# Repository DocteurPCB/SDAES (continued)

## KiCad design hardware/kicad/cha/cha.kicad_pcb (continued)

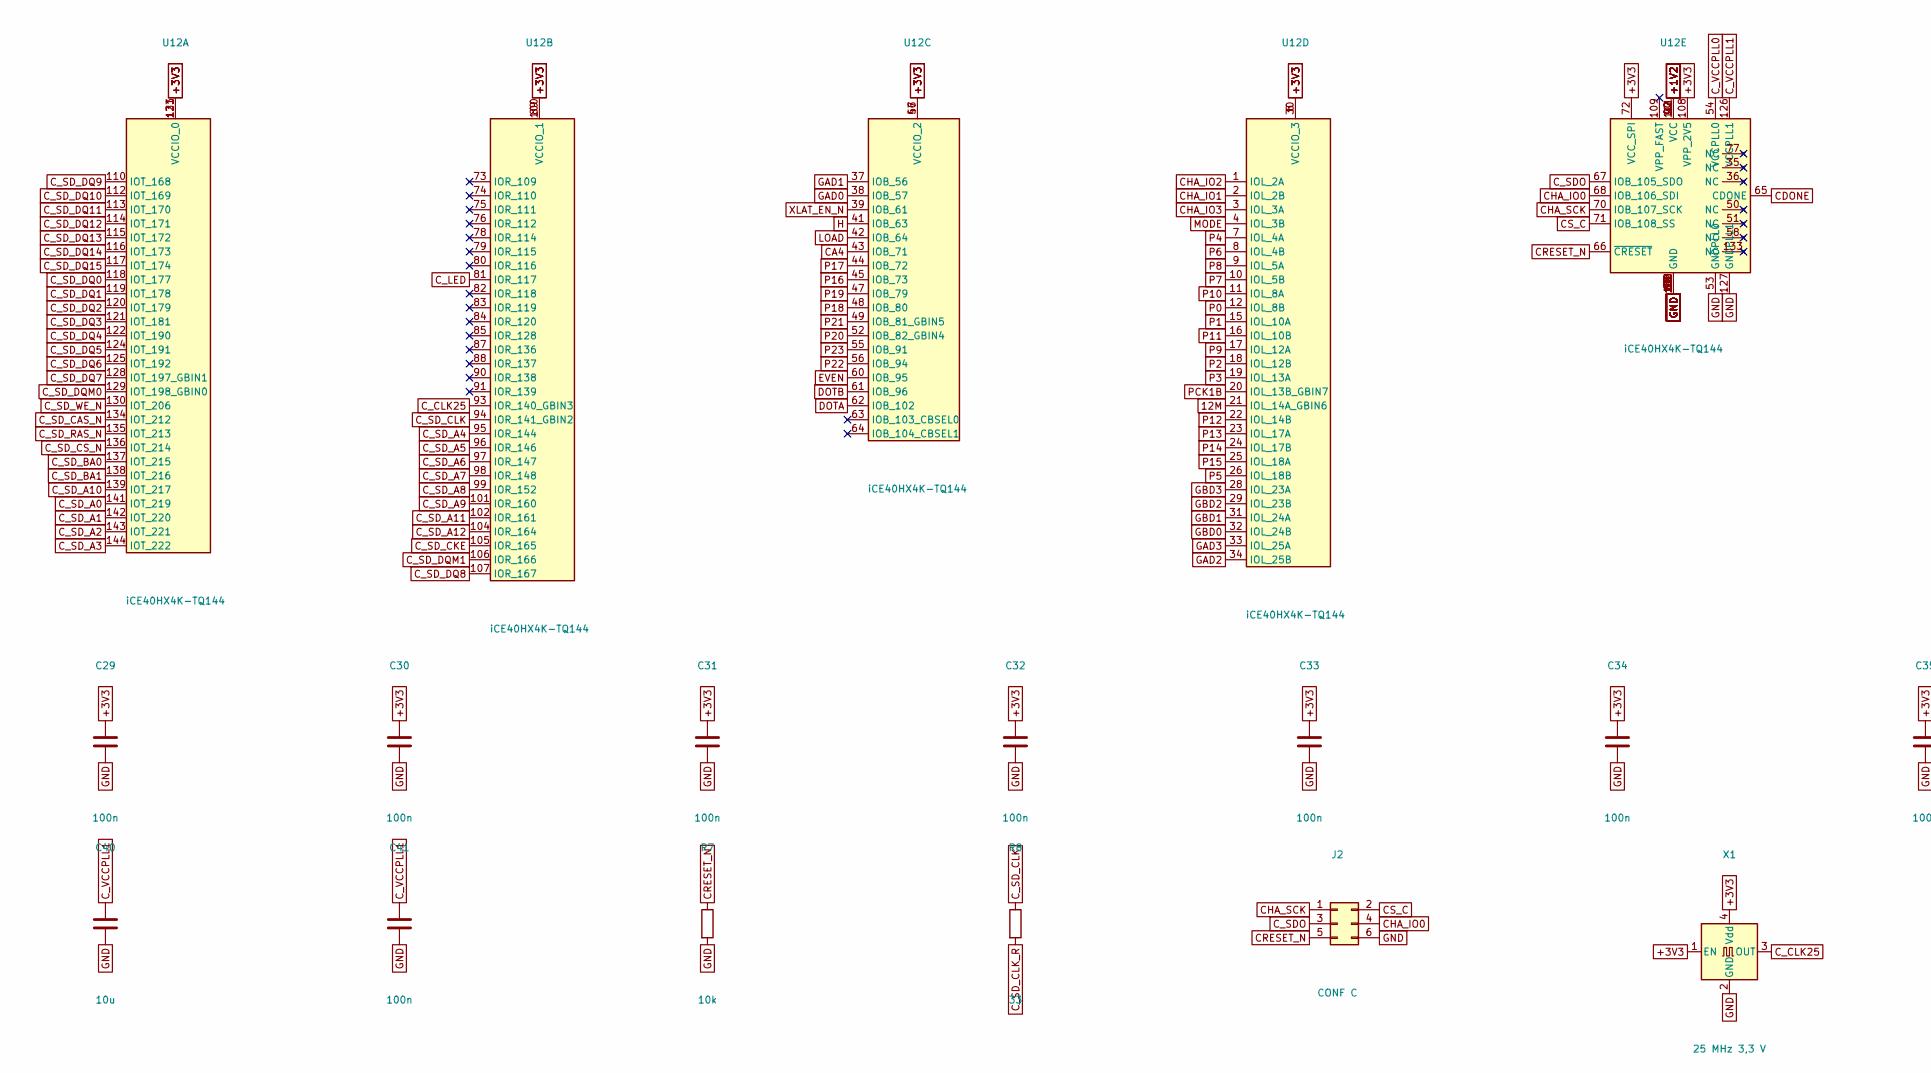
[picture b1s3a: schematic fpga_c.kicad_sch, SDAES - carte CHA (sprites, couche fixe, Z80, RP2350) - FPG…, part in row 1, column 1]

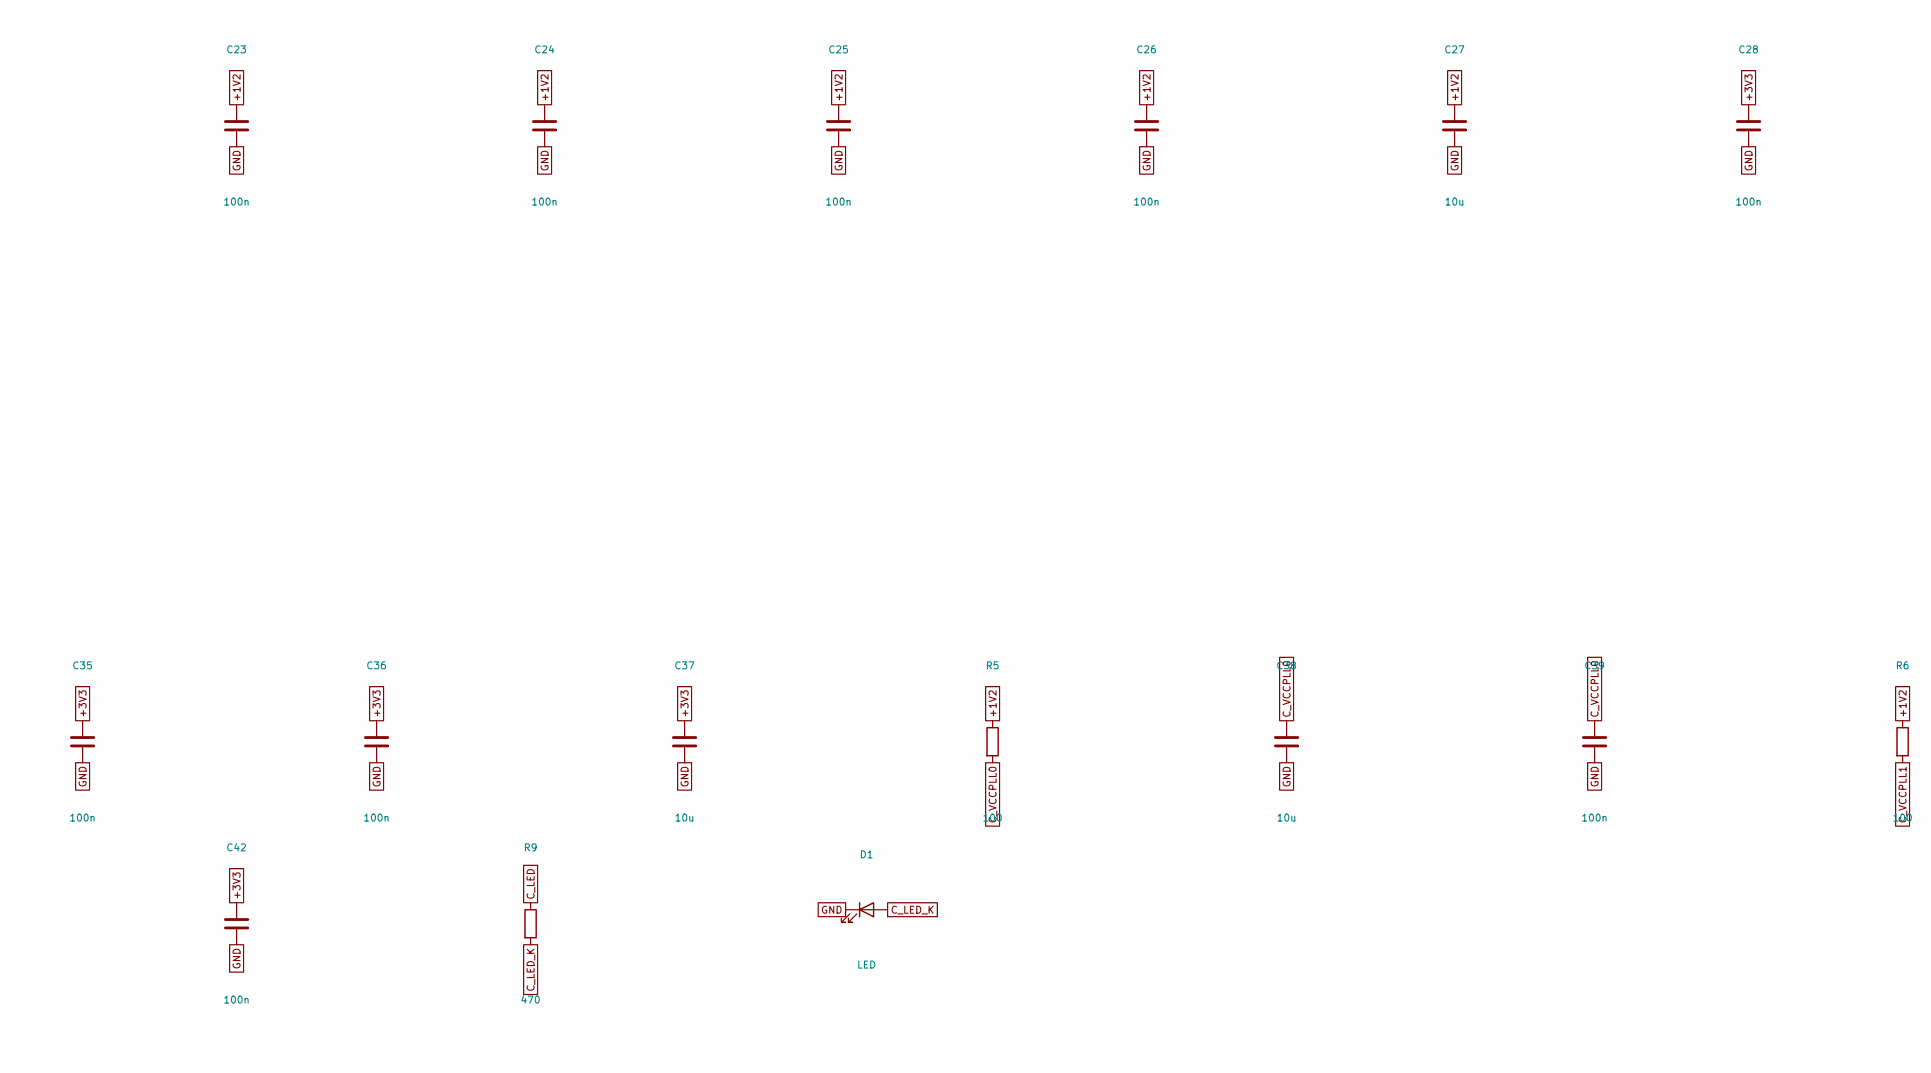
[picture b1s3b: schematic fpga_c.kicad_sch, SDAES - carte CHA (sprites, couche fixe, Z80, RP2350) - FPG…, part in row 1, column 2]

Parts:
C23, C24, C25, C26, C28, C29, C30, C31, C32, C33, C34, C35, C36, C39, C41, C42: 100n; C_0603_1608Metric
C27, C37, C38, C40: 10u; C_0805_2012Metric
D1: LED; LED_0603_1608Metric
J2: CONF C; PinHeader_2x03_P2.54mm_Vertical
R5, R6: 100; R_0603_1608Metric
R7: 10k; R_0603_1608Metric
R8: 33; R_0603_1608Metric
R9: 470; R_0603_1608Metric
U12: iCE40HX4K-TQ144; TQFP-144_20x20mm_P0.5mm
X1: 25 MHz 3,3 V; Oscillator_SMD_Abracon_ASE-4Pin_3.2x2.5mm_HandSoldering

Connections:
12M: U12.21 (IOL_14A_GBIN6); also elsewhere on the board
+1V2: C23.1, C24.1, C25.1, C26.1, C27.1, R5.1, R6.1, U12.27 (VCC), U12.40 (VCC), U12.92 (VCC), U12.111 (VCC); also elsewhere on the board
+3V3: C28.1, C29.1, C30.1, C31.1, C32.1, C33.1, C34.1, C35.1, C36.1, C37.1, C42.1, U12.6 (VCCIO_3), U12.30 (VCCIO_3), U12.46 (VCCIO_2), U12.57 (VCCIO_2), U12.72 (VCC_SPI), U12.89 (VCCIO_1), U12.100 (VCCIO_1), U12.108 (VPP_2V5), U12.123 (VCCIO_0), U12.131 (VCCIO_0), X1.1 (EN), X1.4 (Vdd); also elsewhere on the board
CA4: U12.43 (IOB_71); also elsewhere on the board
CDONE: U12.65 (CDONE); also elsewhere on the board
CHA_IO0: J2.4, U12.68 (IOB_106_SDI); also elsewhere on the board
CHA_IO1: U12.2 (IOL_2B); also elsewhere on the board
CHA_IO2: U12.1 (IOL_2A); also elsewhere on the board
CHA_IO3: U12.3 (IOL_3A); also elsewhere on the board
CHA_SCK: J2.1, U12.70 (IOB_107_SCK); also elsewhere on the board
CRESET_N: J2.5, R7.1, U12.66 (~CRESET); also elsewhere on the board
CS_C: J2.2, U12.71 (IOB_108_SS); also elsewhere on the board
C_CLK25: U12.93 (IOR_140_GBIN3), X1.3 (OUT)
C_LED: R9.1, U12.81 (IOR_117)
C_LED_K: D1.2 (A), R9.2
C_SDO: J2.3, U12.67 (IOB_105_SDO)
C_SD_A0: U12.141 (IOT_219); also elsewhere on the board
C_SD_A1: U12.142 (IOT_220); also elsewhere on the board
C_SD_A2: U12.143 (IOT_221); also elsewhere on the board
C_SD_A3: U12.144 (IOT_222); also elsewhere on the board
C_SD_A4: U12.95 (IOR_144); also elsewhere on the board
C_SD_A5: U12.96 (IOR_146); also elsewhere on the board
C_SD_A6: U12.97 (IOR_147); also elsewhere on the board
C_SD_A7: U12.98 (IOR_148); also elsewhere on the board
C_SD_A8: U12.99 (IOR_152); also elsewhere on the board
C_SD_A9: U12.101 (IOR_160); also elsewhere on the board
C_SD_A10: U12.139 (IOT_217); also elsewhere on the board
C_SD_A11: U12.102 (IOR_161); also elsewhere on the board
C_SD_A12: U12.104 (IOR_164); also elsewhere on the board
C_SD_BA0: U12.137 (IOT_215); also elsewhere on the board
C_SD_BA1: U12.138 (IOT_216); also elsewhere on the board
C_SD_CAS_N: U12.134 (IOT_212); also elsewhere on the board
C_SD_CKE: U12.105 (IOR_165); also elsewhere on the board
C_SD_CLK: R8.1, U12.94 (IOR_141_GBIN2)
C_SD_CLK_R: R8.2; also elsewhere on the board
C_SD_CS_N: U12.136 (IOT_214); also elsewhere on the board
C_SD_DQ0: U12.118 (IOT_177); also elsewhere on the board
C_SD_DQ1: U12.119 (IOT_178); also elsewhere on the board
C_SD_DQ2: U12.120 (IOT_179); also elsewhere on the board
C_SD_DQ3: U12.121 (IOT_181); also elsewhere on the board
C_SD_DQ4: U12.122 (IOT_190); also elsewhere on the board
C_SD_DQ5: U12.124 (IOT_191); also elsewhere on the board
C_SD_DQ6: U12.125 (IOT_192); also elsewhere on the board
C_SD_DQ7: U12.128 (IOT_197_GBIN1); also elsewhere on the board
C_SD_DQ8: U12.107 (IOR_167); also elsewhere on the board
C_SD_DQ9: U12.110 (IOT_168); also elsewhere on the board
C_SD_DQ10: U12.112 (IOT_169); also elsewhere on the board
C_SD_DQ11: U12.113 (IOT_170); also elsewhere on the board
C_SD_DQ12: U12.114 (IOT_171); also elsewhere on the board
C_SD_DQ13: U12.115 (IOT_172); also elsewhere on the board
C_SD_DQ14: U12.116 (IOT_173); also elsewhere on the board
C_SD_DQ15: U12.117 (IOT_174); also elsewhere on the board
C_SD_DQM0: U12.129 (IOT_198_GBIN0); also elsewhere on the board
C_SD_DQM1: U12.106 (IOR_166); also elsewhere on the board
C_SD_RAS_N: U12.135 (IOT_213); also elsewhere on the board
C_SD_WE_N: U12.130 (IOT_206); also elsewhere on the board
C_VCCPLL0: C38.1, C39.1, R5.2, U12.54 (VCCPLL0)
C_VCCPLL1: C40.1, C41.1, R6.2, U12.126 (VCCPLL1)
DOTA: U12.62 (IOB_102); also elsewhere on the board
DOTB: U12.61 (IOB_96); also elsewhere on the board
EVEN: U12.60 (IOB_95); also elsewhere on the board
GAD0: U12.38 (IOB_57); also elsewhere on the board
GAD1: U12.37 (IOB_56); also elsewhere on the board
GAD2: U12.34 (IOL_25B); also elsewhere on the board
GAD3: U12.33 (IOL_25A); also elsewhere on the board
GBD0: U12.32 (IOL_24B); also elsewhere on the board
GBD1: U12.31 (IOL_24A); also elsewhere on the board
GBD2: U12.29 (IOL_23B); also elsewhere on the board
GBD3: U12.28 (IOL_23A); also elsewhere on the board
GND: C23.2, C24.2, C25.2, C26.2, C27.2, C28.2, C29.2, C30.2, C31.2, C32.2, C33.2, C34.2, C35.2, C36.2, C37.2, C38.2, C39.2, C40.2, C41.2, C42.2, D1.1 (K), J2.6, R7.2, U12.5 (GND), U12.13 (GND), U12.14 (GND), U12.53 (GNDPLL0), U12.59 (GND), U12.69 (GND), U12.86 (GND), U12.103 (GND), U12.127 (GNDPLL1), U12.132 (GND), U12.140 (GND), X1.2 (GND); also elsewhere on the board
H: U12.41 (IOB_63); also elsewhere on the board
LOAD: U12.42 (IOB_64); also elsewhere on the board
MODE: U12.4 (IOL_3B); also elsewhere on the board
P0: U12.12 (IOL_8B); also elsewhere on the board
P1: U12.15 (IOL_10A); also elsewhere on the board
P2: U12.18 (IOL_12B); also elsewhere on the board
P3: U12.19 (IOL_13A); also elsewhere on the board
P4: U12.7 (IOL_4A); also elsewhere on the board
P5: U12.26 (IOL_18B); also elsewhere on the board
P6: U12.8 (IOL_4B); also elsewhere on the board
P7: U12.10 (IOL_5B); also elsewhere on the board
P8: U12.9 (IOL_5A); also elsewhere on the board
P9: U12.17 (IOL_12A); also elsewhere on the board
P10: U12.11 (IOL_8A); also elsewhere on the board
P11: U12.16 (IOL_10B); also elsewhere on the board
P12: U12.22 (IOL_14B); also elsewhere on the board
P13: U12.23 (IOL_17A); also elsewhere on the board
P14: U12.24 (IOL_17B); also elsewhere on the board
P15: U12.25 (IOL_18A); also elsewhere on the board
P16: U12.45 (IOB_73); also elsewhere on the board
P17: U12.44 (IOB_72); also elsewhere on the board
P18: U12.48 (IOB_80); also elsewhere on the board
P19: U12.47 (IOB_79); also elsewhere on the board
P20: U12.52 (IOB_82_GBIN4); also elsewhere on the board
P21: U12.49 (IOB_81_GBIN5); also elsewhere on the board
P22: U12.56 (IOB_94); also elsewhere on the board
P23: U12.55 (IOB_91); also elsewhere on the board
PCK1B: U12.20 (IOL_13B_GBIN7); also elsewhere on the board
XLAT_EN_N: U12.39 (IOB_61); also elsewhere on the board

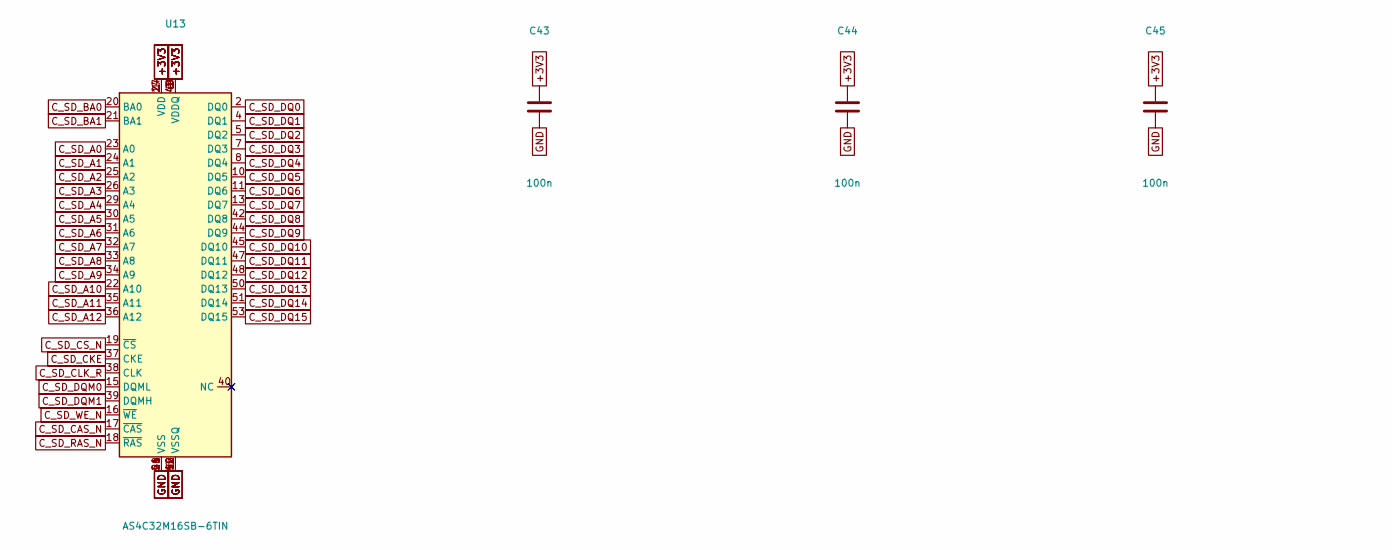
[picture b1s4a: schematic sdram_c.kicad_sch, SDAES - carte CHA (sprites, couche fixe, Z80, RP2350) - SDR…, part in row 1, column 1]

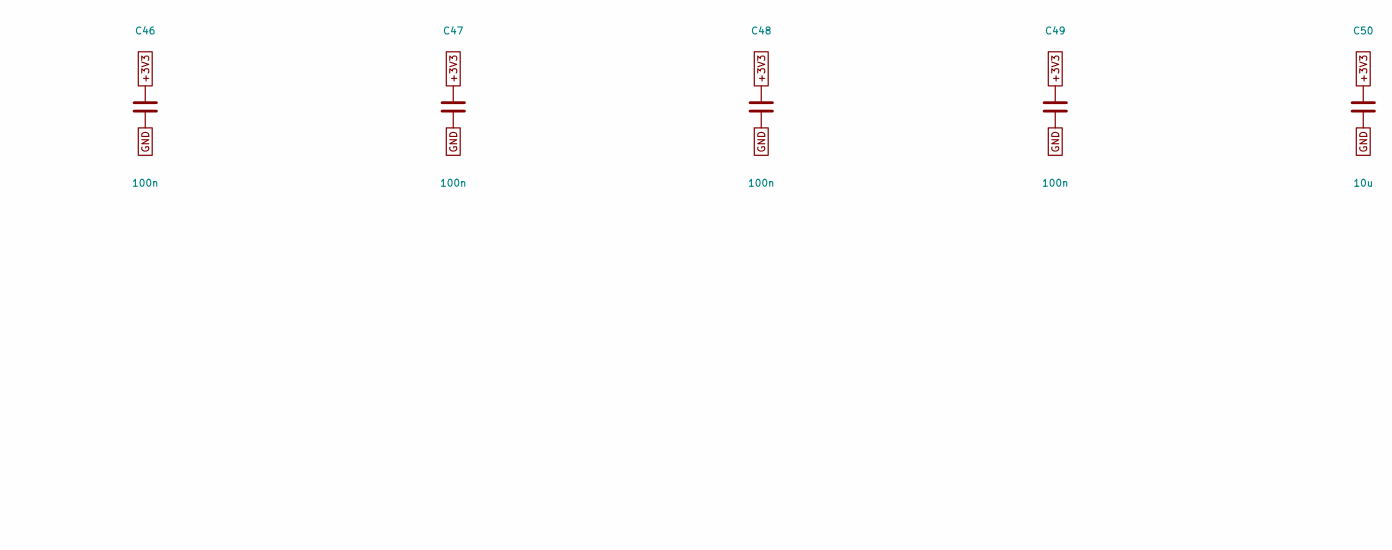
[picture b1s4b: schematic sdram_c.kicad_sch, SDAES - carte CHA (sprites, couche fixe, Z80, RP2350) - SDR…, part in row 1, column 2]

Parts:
C43, C44, C45, C46, C47, C48, C49: 100n; C_0603_1608Metric
C50: 10u; C_0805_2012Metric
U13: AS4C32M16SB-6TIN; TSOP-II-54_22.2x10.16mm_P0.8mm

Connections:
+3V3: C43.1, C44.1, C45.1, C46.1, C47.1, C48.1, C49.1, C50.1, U13.1 (VDD), U13.3 (VDDQ), U13.9 (VDDQ), U13.14 (VDD), U13.27 (VDD), U13.43 (VDDQ), U13.49 (VDDQ); also elsewhere on the board
C_SD_A0: U13.23 (A0); also elsewhere on the board
C_SD_A1: U13.24 (A1); also elsewhere on the board
C_SD_A2: U13.25 (A2); also elsewhere on the board
C_SD_A3: U13.26 (A3); also elsewhere on the board
C_SD_A4: U13.29 (A4); also elsewhere on the board
C_SD_A5: U13.30 (A5); also elsewhere on the board
C_SD_A6: U13.31 (A6); also elsewhere on the board
C_SD_A7: U13.32 (A7); also elsewhere on the board
C_SD_A8: U13.33 (A8); also elsewhere on the board
C_SD_A9: U13.34 (A9); also elsewhere on the board
C_SD_A10: U13.22 (A10); also elsewhere on the board
C_SD_A11: U13.35 (A11); also elsewhere on the board
C_SD_A12: U13.36 (A12); also elsewhere on the board
C_SD_BA0: U13.20 (BA0); also elsewhere on the board
C_SD_BA1: U13.21 (BA1); also elsewhere on the board
C_SD_CAS_N: U13.17 (~CAS); also elsewhere on the board
C_SD_CKE: U13.37 (CKE); also elsewhere on the board
C_SD_CLK_R: U13.38 (CLK); also elsewhere on the board
C_SD_CS_N: U13.19 (~CS); also elsewhere on the board
C_SD_DQ0: U13.2 (DQ0); also elsewhere on the board
C_SD_DQ1: U13.4 (DQ1); also elsewhere on the board
C_SD_DQ2: U13.5 (DQ2); also elsewhere on the board
C_SD_DQ3: U13.7 (DQ3); also elsewhere on the board
C_SD_DQ4: U13.8 (DQ4); also elsewhere on the board
C_SD_DQ5: U13.10 (DQ5); also elsewhere on the board
C_SD_DQ6: U13.11 (DQ6); also elsewhere on the board
C_SD_DQ7: U13.13 (DQ7); also elsewhere on the board
C_SD_DQ8: U13.42 (DQ8); also elsewhere on the board
C_SD_DQ9: U13.44 (DQ9); also elsewhere on the board
C_SD_DQ10: U13.45 (DQ10); also elsewhere on the board
C_SD_DQ11: U13.47 (DQ11); also elsewhere on the board
C_SD_DQ12: U13.48 (DQ12); also elsewhere on the board
C_SD_DQ13: U13.50 (DQ13); also elsewhere on the board
C_SD_DQ14: U13.51 (DQ14); also elsewhere on the board
C_SD_DQ15: U13.53 (DQ15); also elsewhere on the board
C_SD_DQM0: U13.15 (DQML); also elsewhere on the board
C_SD_DQM1: U13.39 (DQMH); also elsewhere on the board
C_SD_RAS_N: U13.18 (~RAS); also elsewhere on the board
C_SD_WE_N: U13.16 (~WE); also elsewhere on the board
GND: C43.2, C44.2, C45.2, C46.2, C47.2, C48.2, C49.2, C50.2, U13.6 (VSSQ), U13.12 (VSSQ), U13.28 (VSS), U13.41 (VSS), U13.46 (VSSQ), U13.52 (VSSQ), U13.54 (VSS); also elsewhere on the board

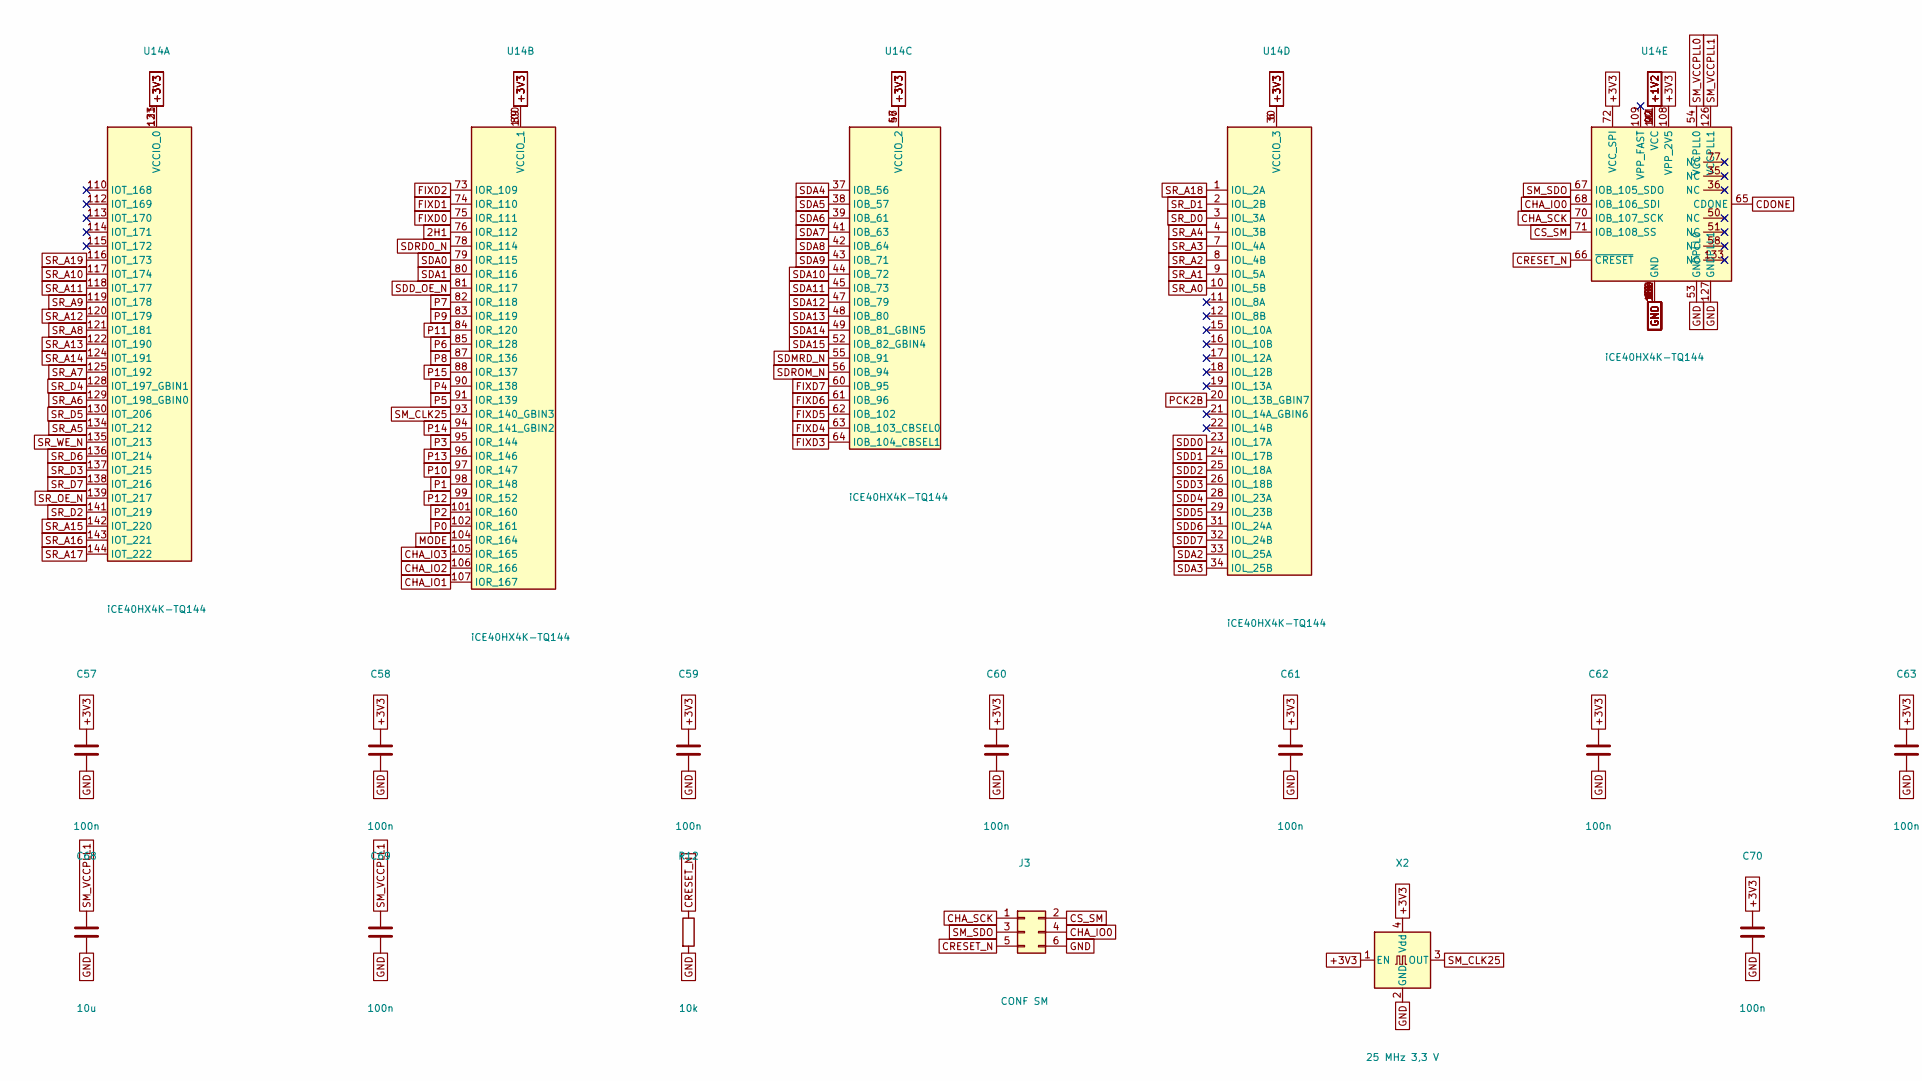
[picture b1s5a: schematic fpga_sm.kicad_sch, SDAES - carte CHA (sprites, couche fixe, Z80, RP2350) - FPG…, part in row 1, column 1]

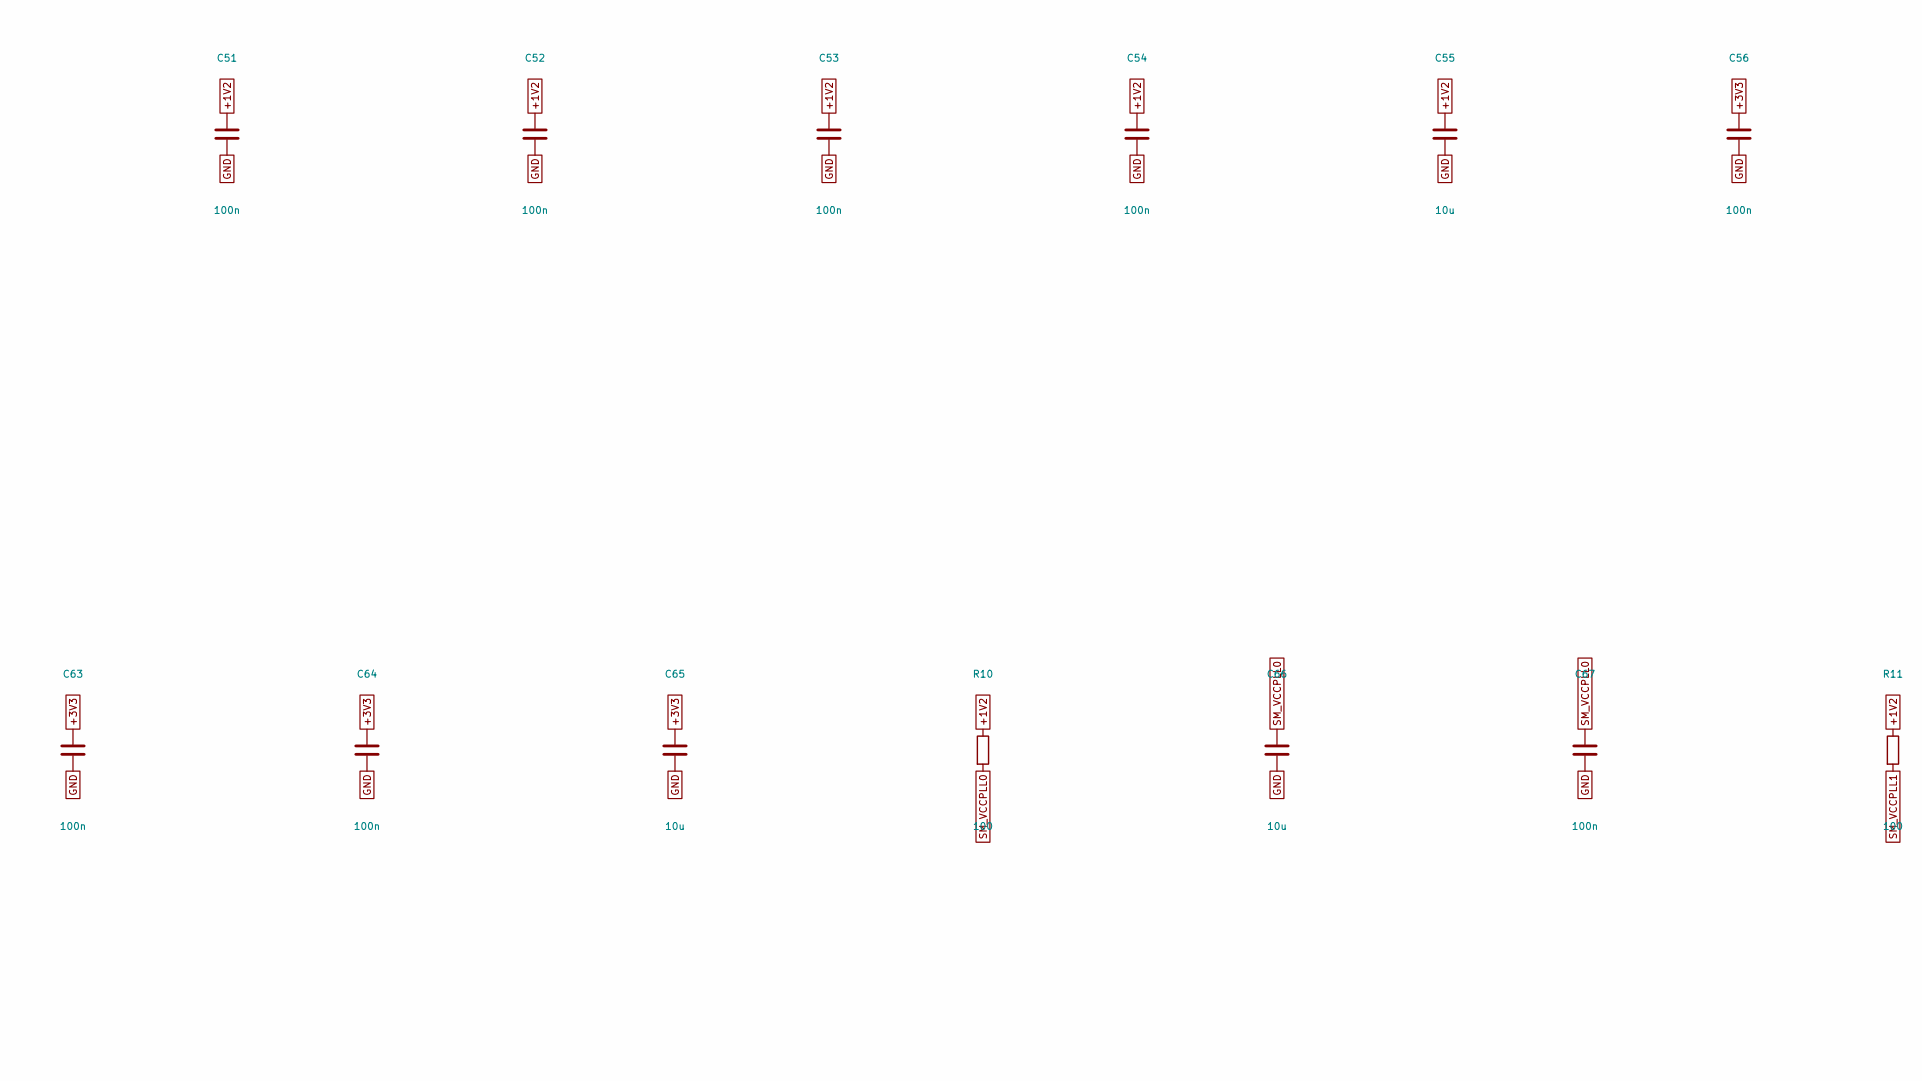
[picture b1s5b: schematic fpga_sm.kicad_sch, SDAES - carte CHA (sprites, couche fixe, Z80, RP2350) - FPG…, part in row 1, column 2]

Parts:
C51, C52, C53, C54, C56, C57, C58, C59, C60, C61, C62, C63, C64, C67, C69, C70: 100n; C_0603_1608Metric
C55, C65, C66, C68: 10u; C_0805_2012Metric
J3: CONF SM; PinHeader_2x03_P2.54mm_Vertical
R10, R11: 100; R_0603_1608Metric
R12: 10k; R_0603_1608Metric
U14: iCE40HX4K-TQ144; TQFP-144_20x20mm_P0.5mm
X2: 25 MHz 3,3 V; Oscillator_SMD_Abracon_ASE-4Pin_3.2x2.5mm_HandSoldering

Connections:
2H1: U14.76 (IOR_112); also elsewhere on the board
+1V2: C51.1, C52.1, C53.1, C54.1, C55.1, R10.1, R11.1, U14.27 (VCC), U14.40 (VCC), U14.92 (VCC), U14.111 (VCC); also elsewhere on the board
+3V3: C56.1, C57.1, C58.1, C59.1, C60.1, C61.1, C62.1, C63.1, C64.1, C65.1, C70.1, U14.6 (VCCIO_3), U14.30 (VCCIO_3), U14.46 (VCCIO_2), U14.57 (VCCIO_2), U14.72 (VCC_SPI), U14.89 (VCCIO_1), U14.100 (VCCIO_1), U14.108 (VPP_2V5), U14.123 (VCCIO_0), U14.131 (VCCIO_0), X2.1 (EN), X2.4 (Vdd); also elsewhere on the board
CDONE: U14.65 (CDONE); also elsewhere on the board
CHA_IO0: J3.4, U14.68 (IOB_106_SDI); also elsewhere on the board
CHA_IO1: U14.107 (IOR_167); also elsewhere on the board
CHA_IO2: U14.106 (IOR_166); also elsewhere on the board
CHA_IO3: U14.105 (IOR_165); also elsewhere on the board
CHA_SCK: J3.1, U14.70 (IOB_107_SCK); also elsewhere on the board
CRESET_N: J3.5, R12.1, U14.66 (~CRESET); also elsewhere on the board
CS_SM: J3.2, U14.71 (IOB_108_SS); also elsewhere on the board
FIXD0: U14.75 (IOR_111); also elsewhere on the board
FIXD1: U14.74 (IOR_110); also elsewhere on the board
FIXD2: U14.73 (IOR_109); also elsewhere on the board
FIXD3: U14.64 (IOB_104_CBSEL1); also elsewhere on the board
FIXD4: U14.63 (IOB_103_CBSEL0); also elsewhere on the board
FIXD5: U14.62 (IOB_102); also elsewhere on the board
FIXD6: U14.61 (IOB_96); also elsewhere on the board
FIXD7: U14.60 (IOB_95); also elsewhere on the board
GND: C51.2, C52.2, C53.2, C54.2, C55.2, C56.2, C57.2, C58.2, C59.2, C60.2, C61.2, C62.2, C63.2, C64.2, C65.2, C66.2, C67.2, C68.2, C69.2, C70.2, J3.6, R12.2, U14.5 (GND), U14.13 (GND), U14.14 (GND), U14.53 (GNDPLL0), U14.59 (GND), U14.69 (GND), U14.86 (GND), U14.103 (GND), U14.127 (GNDPLL1), U14.132 (GND), U14.140 (GND), X2.2 (GND); also elsewhere on the board
MODE: U14.104 (IOR_164); also elsewhere on the board
P0: U14.102 (IOR_161); also elsewhere on the board
P1: U14.98 (IOR_148); also elsewhere on the board
P2: U14.101 (IOR_160); also elsewhere on the board
P3: U14.95 (IOR_144); also elsewhere on the board
P4: U14.90 (IOR_138); also elsewhere on the board
P5: U14.91 (IOR_139); also elsewhere on the board
P6: U14.85 (IOR_128); also elsewhere on the board
P7: U14.82 (IOR_118); also elsewhere on the board
P8: U14.87 (IOR_136); also elsewhere on the board
P9: U14.83 (IOR_119); also elsewhere on the board
P10: U14.97 (IOR_147); also elsewhere on the board
P11: U14.84 (IOR_120); also elsewhere on the board
P12: U14.99 (IOR_152); also elsewhere on the board
P13: U14.96 (IOR_146); also elsewhere on the board
P14: U14.94 (IOR_141_GBIN2); also elsewhere on the board
P15: U14.88 (IOR_137); also elsewhere on the board
PCK2B: U14.20 (IOL_13B_GBIN7); also elsewhere on the board
SDA0: U14.79 (IOR_115); also elsewhere on the board
SDA1: U14.80 (IOR_116); also elsewhere on the board
SDA2: U14.33 (IOL_25A); also elsewhere on the board
SDA3: U14.34 (IOL_25B); also elsewhere on the board
SDA4: U14.37 (IOB_56); also elsewhere on the board
SDA5: U14.38 (IOB_57); also elsewhere on the board
SDA6: U14.39 (IOB_61); also elsewhere on the board
SDA7: U14.41 (IOB_63); also elsewhere on the board
SDA8: U14.42 (IOB_64); also elsewhere on the board
SDA9: U14.43 (IOB_71); also elsewhere on the board
SDA10: U14.44 (IOB_72); also elsewhere on the board
SDA11: U14.45 (IOB_73); also elsewhere on the board
SDA12: U14.47 (IOB_79); also elsewhere on the board
SDA13: U14.48 (IOB_80); also elsewhere on the board
SDA14: U14.49 (IOB_81_GBIN5); also elsewhere on the board
SDA15: U14.52 (IOB_82_GBIN4); also elsewhere on the board
SDD0: U14.23 (IOL_17A); also elsewhere on the board
SDD1: U14.24 (IOL_17B); also elsewhere on the board
SDD2: U14.25 (IOL_18A); also elsewhere on the board
SDD3: U14.26 (IOL_18B); also elsewhere on the board
SDD4: U14.28 (IOL_23A); also elsewhere on the board
SDD5: U14.29 (IOL_23B); also elsewhere on the board
SDD6: U14.31 (IOL_24A); also elsewhere on the board
SDD7: U14.32 (IOL_24B); also elsewhere on the board
SDD_OE_N: U14.81 (IOR_117); also elsewhere on the board
SDMRD_N: U14.55 (IOB_91); also elsewhere on the board
SDRD0_N: U14.78 (IOR_114); also elsewhere on the board
SDROM_N: U14.56 (IOB_94); also elsewhere on the board
SM_CLK25: U14.93 (IOR_140_GBIN3), X2.3 (OUT)
SM_SDO: J3.3, U14.67 (IOB_105_SDO)
SM_VCCPLL0: C66.1, C67.1, R10.2, U14.54 (VCCPLL0)
SM_VCCPLL1: C68.1, C69.1, R11.2, U14.126 (VCCPLL1)
SR_A0: U14.10 (IOL_5B); also elsewhere on the board
SR_A1: U14.9 (IOL_5A); also elsewhere on the board
SR_A2: U14.8 (IOL_4B); also elsewhere on the board
SR_A3: U14.7 (IOL_4A); also elsewhere on the board
SR_A4: U14.4 (IOL_3B); also elsewhere on the board
SR_A5: U14.134 (IOT_212); also elsewhere on the board
SR_A6: U14.129 (IOT_198_GBIN0); also elsewhere on the board
SR_A7: U14.125 (IOT_192); also elsewhere on the board
SR_A8: U14.121 (IOT_181); also elsewhere on the board
SR_A9: U14.119 (IOT_178); also elsewhere on the board
SR_A10: U14.117 (IOT_174); also elsewhere on the board
SR_A11: U14.118 (IOT_177); also elsewhere on the board
SR_A12: U14.120 (IOT_179); also elsewhere on the board
SR_A13: U14.122 (IOT_190); also elsewhere on the board
SR_A14: U14.124 (IOT_191); also elsewhere on the board
SR_A15: U14.142 (IOT_220); also elsewhere on the board
SR_A16: U14.143 (IOT_221); also elsewhere on the board
SR_A17: U14.144 (IOT_222); also elsewhere on the board
SR_A18: U14.1 (IOL_2A); also elsewhere on the board
SR_A19: U14.116 (IOT_173); also elsewhere on the board
SR_D0: U14.3 (IOL_3A); also elsewhere on the board
SR_D1: U14.2 (IOL_2B); also elsewhere on the board
SR_D2: U14.141 (IOT_219); also elsewhere on the board
SR_D3: U14.137 (IOT_215); also elsewhere on the board
SR_D4: U14.128 (IOT_197_GBIN1); also elsewhere on the board
SR_D5: U14.130 (IOT_206); also elsewhere on the board
SR_D6: U14.136 (IOT_214); also elsewhere on the board
SR_D7: U14.138 (IOT_216); also elsewhere on the board
SR_OE_N: U14.139 (IOT_217); also elsewhere on the board
SR_WE_N: U14.135 (IOT_213); also elsewhere on the board

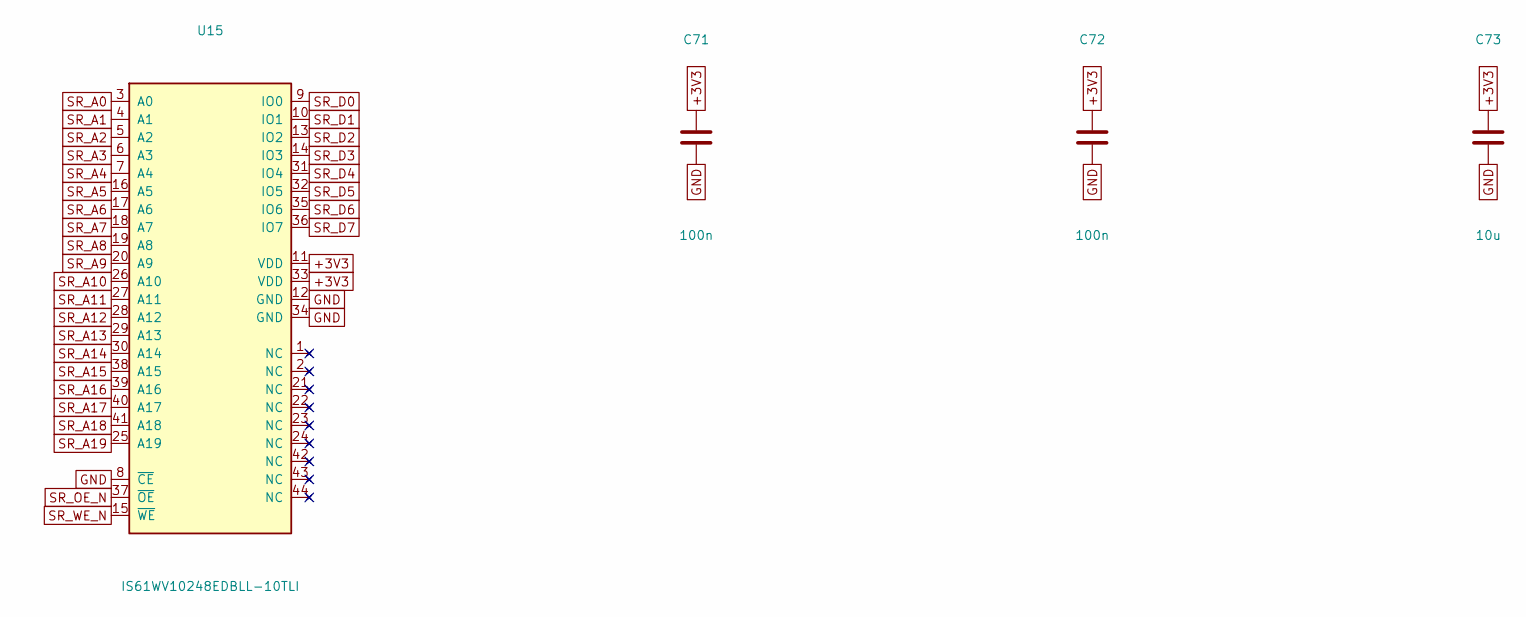
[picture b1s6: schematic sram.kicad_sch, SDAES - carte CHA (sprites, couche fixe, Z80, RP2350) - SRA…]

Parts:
C71, C72: 100n; C_0603_1608Metric
C73: 10u; C_0805_2012Metric
U15: IS61WV10248EDBLL-10TLI; TSOP-II-44_10.16x18.41mm_P0.8mm

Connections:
+3V3: C71.1, C72.1, C73.1, U15.11 (VDD), U15.33 (VDD); also elsewhere on the board
GND: C71.2, C72.2, C73.2, U15.8 (~CE), U15.12 (GND), U15.34 (GND); also elsewhere on the board
SR_A0: U15.3 (A0); also elsewhere on the board
SR_A1: U15.4 (A1); also elsewhere on the board
SR_A2: U15.5 (A2); also elsewhere on the board
SR_A3: U15.6 (A3); also elsewhere on the board
SR_A4: U15.7 (A4); also elsewhere on the board
SR_A5: U15.16 (A5); also elsewhere on the board
SR_A6: U15.17 (A6); also elsewhere on the board
SR_A7: U15.18 (A7); also elsewhere on the board
SR_A8: U15.19 (A8); also elsewhere on the board
SR_A9: U15.20 (A9); also elsewhere on the board
SR_A10: U15.26 (A10); also elsewhere on the board
SR_A11: U15.27 (A11); also elsewhere on the board
SR_A12: U15.28 (A12); also elsewhere on the board
SR_A13: U15.29 (A13); also elsewhere on the board
SR_A14: U15.30 (A14); also elsewhere on the board
SR_A15: U15.38 (A15); also elsewhere on the board
SR_A16: U15.39 (A16); also elsewhere on the board
SR_A17: U15.40 (A17); also elsewhere on the board
SR_A18: U15.41 (A18); also elsewhere on the board
SR_A19: U15.25 (A19); also elsewhere on the board
SR_D0: U15.9 (IO0); also elsewhere on the board
SR_D1: U15.10 (IO1); also elsewhere on the board
SR_D2: U15.13 (IO2); also elsewhere on the board
SR_D3: U15.14 (IO3); also elsewhere on the board
SR_D4: U15.31 (IO4); also elsewhere on the board
SR_D5: U15.32 (IO5); also elsewhere on the board
SR_D6: U15.35 (IO6); also elsewhere on the board
SR_D7: U15.36 (IO7); also elsewhere on the board
SR_OE_N: U15.37 (~OE); also elsewhere on the board
SR_WE_N: U15.15 (~WE); also elsewhere on the board

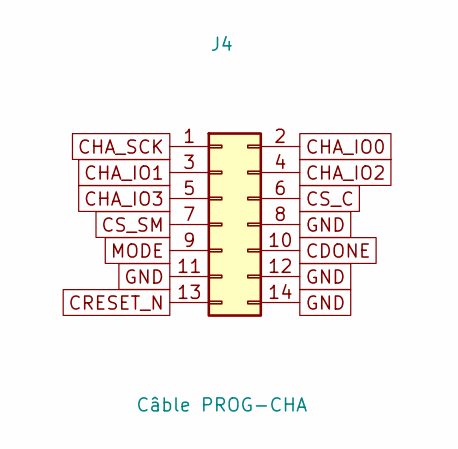
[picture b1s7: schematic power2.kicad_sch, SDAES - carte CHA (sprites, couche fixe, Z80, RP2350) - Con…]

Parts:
J4: Câble PROG-CHA; PinHeader_2x07_P2.54mm_Vertical

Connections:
CDONE: J4.10; also elsewhere on the board
CHA_IO0: J4.2; also elsewhere on the board
CHA_IO1: J4.3; also elsewhere on the board
CHA_IO2: J4.4; also elsewhere on the board
CHA_IO3: J4.5; also elsewhere on the board
CHA_SCK: J4.1; also elsewhere on the board
CRESET_N: J4.13; also elsewhere on the board
CS_C: J4.6; also elsewhere on the board
CS_SM: J4.7; also elsewhere on the board
GND: J4.8, J4.11, J4.12, J4.14; also elsewhere on the board
MODE: J4.9; also elsewhere on the board
